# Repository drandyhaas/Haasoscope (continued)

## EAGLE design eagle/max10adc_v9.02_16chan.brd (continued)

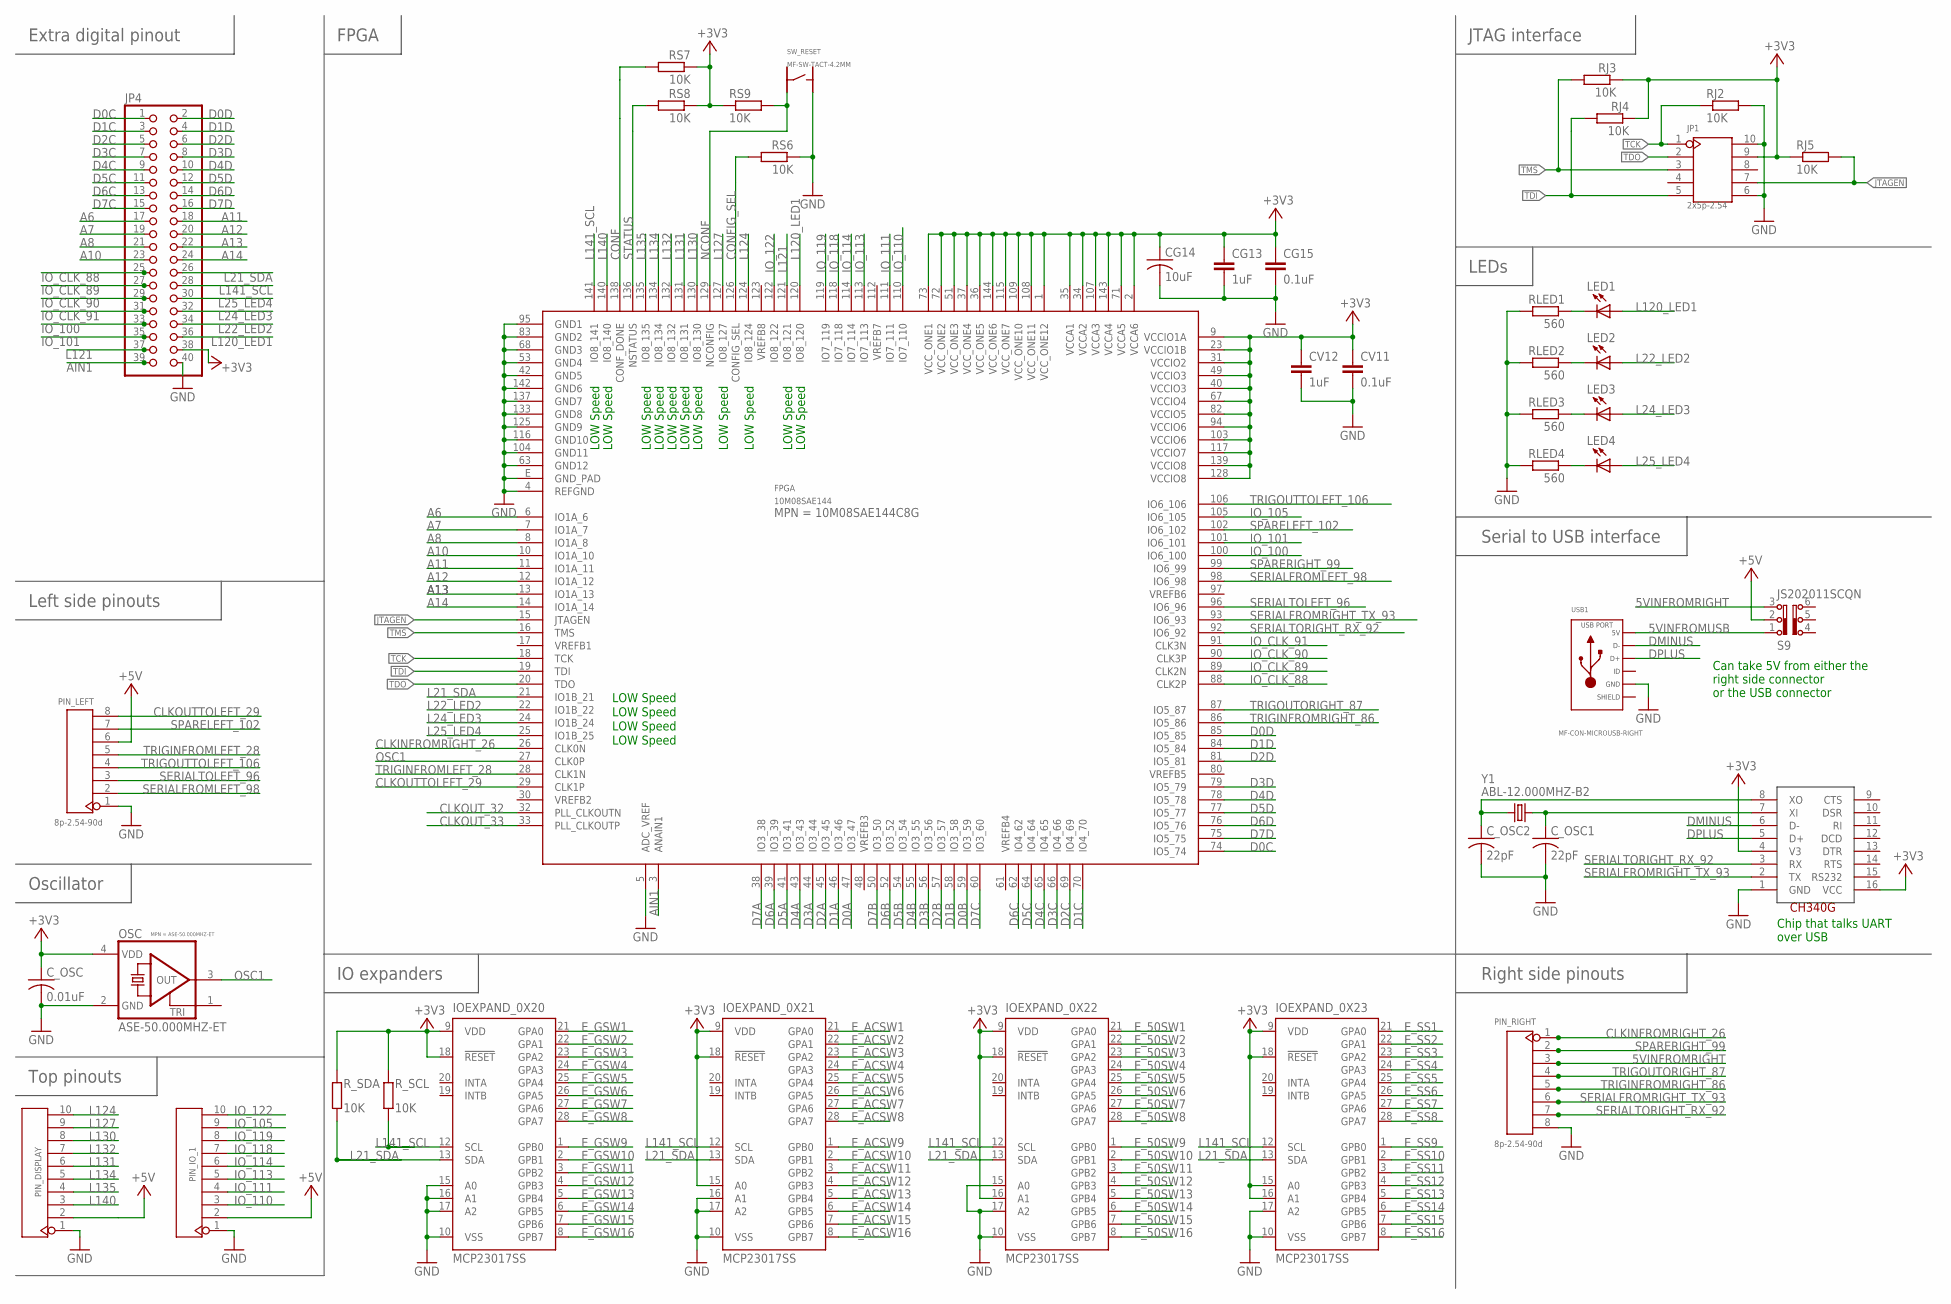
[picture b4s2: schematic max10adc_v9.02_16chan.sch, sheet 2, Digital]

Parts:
CG13: 1uF; C0805K; MPN MF-CAP-0805-1uF
CG14: 10uF; C1206; MPN MF-CAP-1206-10uF
CG15: 0.1uF; C0805K; MPN MF-CAP-0805-0.1uF
CV11: 0.1uF; C0805K; MPN MF-CAP-0805-0.1uF
CV12: 1uF; C0805K; MPN MF-CAP-0805-1uF
C_OSC: 0.01uF; C0603
C_OSC1, C_OSC2: 22pF; C0603
FPGA: 10M08SAE144; EQFP144; MPN 10M08SAE144C8G
IOEXPAND_0X20, IOEXPAND_0X21, IOEXPAND_0X22, IOEXPAND_0X23: MCP23017SS; SSOP28
JP1: 2x5p-2.54; H2X5-2.54
JP4: PINHD-2X20/90; 2X20/90
LED1, LED2, LED3, LED4: MF-LED-0805-RED; SML0805; MPN MF-LED-0805-RED
OSC: ASE-50.000MHZ-ET; ASE; MPN ASE-50.000MHZ-ET
PIN_DISPLAY: YELLOW-10P-2.54; H10-2.54
PIN_IO_1: YELLOW-10P-2.54; H10-2.54
PIN_LEFT: 8p-2.54-90d; H8-2.54-90D-MALE
PIN_RIGHT: 8p-2.54-90d; H8-2.54-90D-FEMALE
RJ2, RJ3, RJ4, RJ5: 10K; R0805; MPN MF-RES-0805-10K
RLED1, RLED2, RLED3, RLED4: 560; R0805; MPN MF-RES-0805-560
RS6, RS7, RS8, RS9: 10K; R0805; MPN MF-RES-0805-10K
R_SCL: 10K; R0805; MPN MF-RES-0805-10K
R_SDA: 10K; R0805; MPN MF-RES-0805-10K
S9: JS202011SCQN
SW_RESET: MF-SW-TACT-4.2MM; TACT4.2MM
U340G: CH340G; SOIC16
USB1: MF-CON-MICROUSB-RIGHT; 10118193-0001LF
Y1: ABL-12.000MHZ-B2; HC49US

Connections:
5VINFROMRIGHT: PIN_RIGHT.3, S9.3
5VINFROMUSB: S9.1, USB1.1 (5V)
+3V3: CG13.1, CG14.1, CG15.1, CV11.1, CV12.1, C_OSC.1, FPGA.1 (VCC_ONE12), FPGA.2 (VCCA6), FPGA.9 (VCCIO1A), FPGA.23 (VCCIO1B), FPGA.31 (VCCIO2), FPGA.34 (VCCA2), FPGA.35 (VCCA1), FPGA.36 (VCC_ONE5), FPGA.37 (VCC_ONE4), FPGA.40 (VCCIO3), FPGA.49 (VCCIO3), FPGA.51 (VCC_ONE3), FPGA.67 (VCCIO4), FPGA.71 (VCCA5), FPGA.72 (VCC_ONE2), FPGA.73 (VCC_ONE1), FPGA.82 (VCCIO5), FPGA.94 (VCCIO6), FPGA.103 (VCCIO6), FPGA.107 (VCCA3), FPGA.108 (VCC_ONE11), FPGA.109 (VCC_ONE10), FPGA.115 (VCC_ONE7), FPGA.117 (VCCIO7), FPGA.128 (VCCIO8), FPGA.139 (VCCIO8), FPGA.143 (VCCA4), FPGA.144 (VCC_ONE6), IOEXPAND_0X20.9 (VDD), IOEXPAND_0X20.18 (!RESET), IOEXPAND_0X21.9 (VDD), IOEXPAND_0X21.15 (A0), IOEXPAND_0X21.18 (!RESET), IOEXPAND_0X22.9 (VDD), IOEXPAND_0X22.16 (A1), IOEXPAND_0X22.18 (!RESET), IOEXPAND_0X23.9 (VDD), IOEXPAND_0X23.15 (A0), IOEXPAND_0X23.16 (A1), IOEXPAND_0X23.18 (!RESET), JP1.9, JP4.38, OSC.4 (VDD), RJ3.1, RJ4.1, RJ5.1, RS7.1, RS8.1, RS9.1, R_SCL.2, R_SDA.2, U340G.4 (V3), U340G.16 (VCC); also elsewhere on the board
+5V: PIN_DISPLAY.2, PIN_IO_1.2, PIN_LEFT.6, S9.2; also elsewhere on the board
A6: FPGA.6 (IO1A_6), JP4.17
A7: FPGA.7 (IO1A_7), JP4.19
A8: FPGA.8 (IO1A_8), JP4.21
A10: FPGA.10 (IO1A_10), JP4.23
A11: FPGA.11 (IO1A_11), JP4.18
A12: FPGA.12 (IO1A_12), JP4.20
A13: FPGA.13 (IO1A_13), JP4.22
A14: FPGA.14 (IO1A_14), JP4.24
AIN1: FPGA.3 (ANAIN1), JP4.39; also elsewhere on the board
CLKINFROMRIGHT_26: FPGA.26 (CLK0N), PIN_RIGHT.1
CLKOUTTOLEFT_29: FPGA.29 (CLK1P), PIN_LEFT.8
CLKOUT_32: FPGA.32 (PLL_CLKOUTN); also elsewhere on the board
CLKOUT_33: FPGA.33 (PLL_CLKOUTP); also elsewhere on the board
CONF: FPGA.138 (CONF_DONE), RS7.2
CONFIG_SEL: FPGA.126 (CONFIG_SEL), RS6.2
D0A: FPGA.47 (IO3_47); also elsewhere on the board
D0B: FPGA.59 (IO3_59); also elsewhere on the board
D0C: FPGA.74 (IO5_74), JP4.1
D0D: FPGA.85 (IO5_85), JP4.2
D1A: FPGA.46 (IO3_46); also elsewhere on the board
D1B: FPGA.58 (IO3_58); also elsewhere on the board
D1C: FPGA.70 (IO4_70), JP4.3
D1D: FPGA.84 (IO5_84), JP4.4
D2A: FPGA.45 (IO3_45); also elsewhere on the board
D2B: FPGA.57 (IO3_57); also elsewhere on the board
D2C: FPGA.69 (IO4_69), JP4.5
D2D: FPGA.81 (IO5_81), JP4.6
D3A: FPGA.44 (IO3_44); also elsewhere on the board
D3B: FPGA.56 (IO3_56); also elsewhere on the board
D3C: FPGA.66 (IO4_66), JP4.7
D3D: FPGA.79 (IO5_79), JP4.8
D4A: FPGA.43 (IO3_43); also elsewhere on the board
D4B: FPGA.55 (IO3_55); also elsewhere on the board
D4C: FPGA.65 (IO4_65), JP4.9
D4D: FPGA.78 (IO5_78), JP4.10
D5A: FPGA.41 (IO3_41); also elsewhere on the board
D5B: FPGA.54 (IO3_54); also elsewhere on the board
D5C: FPGA.64 (IO4_64), JP4.11
D5D: FPGA.77 (IO5_77), JP4.12
D6A: FPGA.39 (IO3_39); also elsewhere on the board
D6B: FPGA.52 (IO3_52); also elsewhere on the board
D6C: FPGA.62 (IO4_62), JP4.13
D6D: FPGA.76 (IO5_76), JP4.14
D7A: FPGA.38 (IO3_38); also elsewhere on the board
D7B: FPGA.50 (IO3_50); also elsewhere on the board
D7C: FPGA.60 (IO3_60), JP4.15
D7D: FPGA.75 (IO5_75), JP4.16
DMINUS: U340G.6 (D-), USB1.2 (D-)
DPLUS: U340G.5 (D+), USB1.3 (D+)
E_50SW1: IOEXPAND_0X22.21 (GPA0); also elsewhere on the board
E_50SW2: IOEXPAND_0X22.22 (GPA1); also elsewhere on the board
E_50SW3: IOEXPAND_0X22.23 (GPA2); also elsewhere on the board
E_50SW4: IOEXPAND_0X22.24 (GPA3); also elsewhere on the board
E_50SW5: IOEXPAND_0X22.25 (GPA4); also elsewhere on the board
E_50SW6: IOEXPAND_0X22.26 (GPA5); also elsewhere on the board
E_50SW7: IOEXPAND_0X22.27 (GPA6); also elsewhere on the board
E_50SW8: IOEXPAND_0X22.28 (GPA7); also elsewhere on the board
E_50SW9: IOEXPAND_0X22.1 (GPB0); also elsewhere on the board
E_50SW10: IOEXPAND_0X22.2 (GPB1); also elsewhere on the board
E_50SW11: IOEXPAND_0X22.3 (GPB2); also elsewhere on the board
E_50SW12: IOEXPAND_0X22.4 (GPB3); also elsewhere on the board
E_50SW13: IOEXPAND_0X22.5 (GPB4); also elsewhere on the board
E_50SW14: IOEXPAND_0X22.6 (GPB5); also elsewhere on the board
E_50SW15: IOEXPAND_0X22.7 (GPB6); also elsewhere on the board
E_50SW16: IOEXPAND_0X22.8 (GPB7); also elsewhere on the board
E_ACSW1: IOEXPAND_0X21.21 (GPA0); also elsewhere on the board
E_ACSW2: IOEXPAND_0X21.22 (GPA1); also elsewhere on the board
E_ACSW3: IOEXPAND_0X21.23 (GPA2); also elsewhere on the board
E_ACSW4: IOEXPAND_0X21.24 (GPA3); also elsewhere on the board
E_ACSW5: IOEXPAND_0X21.25 (GPA4); also elsewhere on the board
E_ACSW6: IOEXPAND_0X21.26 (GPA5); also elsewhere on the board
E_ACSW7: IOEXPAND_0X21.27 (GPA6); also elsewhere on the board
E_ACSW8: IOEXPAND_0X21.28 (GPA7); also elsewhere on the board
E_ACSW9: IOEXPAND_0X21.1 (GPB0); also elsewhere on the board
E_ACSW10: IOEXPAND_0X21.2 (GPB1); also elsewhere on the board
E_ACSW11: IOEXPAND_0X21.3 (GPB2); also elsewhere on the board
E_ACSW12: IOEXPAND_0X21.4 (GPB3); also elsewhere on the board
E_ACSW13: IOEXPAND_0X21.5 (GPB4); also elsewhere on the board
E_ACSW14: IOEXPAND_0X21.6 (GPB5); also elsewhere on the board
E_ACSW15: IOEXPAND_0X21.7 (GPB6); also elsewhere on the board
E_ACSW16: IOEXPAND_0X21.8 (GPB7); also elsewhere on the board
E_GSW1: IOEXPAND_0X20.21 (GPA0); also elsewhere on the board
E_GSW2: IOEXPAND_0X20.22 (GPA1); also elsewhere on the board
E_GSW3: IOEXPAND_0X20.23 (GPA2); also elsewhere on the board
E_GSW4: IOEXPAND_0X20.24 (GPA3); also elsewhere on the board
E_GSW5: IOEXPAND_0X20.25 (GPA4); also elsewhere on the board
E_GSW6: IOEXPAND_0X20.26 (GPA5); also elsewhere on the board
E_GSW7: IOEXPAND_0X20.27 (GPA6); also elsewhere on the board
E_GSW8: IOEXPAND_0X20.28 (GPA7); also elsewhere on the board
E_GSW9: IOEXPAND_0X20.1 (GPB0); also elsewhere on the board
E_GSW10: IOEXPAND_0X20.2 (GPB1); also elsewhere on the board
E_GSW11: IOEXPAND_0X20.3 (GPB2); also elsewhere on the board
E_GSW12: IOEXPAND_0X20.4 (GPB3); also elsewhere on the board
E_GSW13: IOEXPAND_0X20.5 (GPB4); also elsewhere on the board
E_GSW14: IOEXPAND_0X20.6 (GPB5); also elsewhere on the board
E_GSW15: IOEXPAND_0X20.7 (GPB6); also elsewhere on the board
E_GSW16: IOEXPAND_0X20.8 (GPB7); also elsewhere on the board
E_SS1: IOEXPAND_0X23.21 (GPA0); also elsewhere on the board
E_SS2: IOEXPAND_0X23.22 (GPA1); also elsewhere on the board
E_SS3: IOEXPAND_0X23.23 (GPA2); also elsewhere on the board
E_SS4: IOEXPAND_0X23.24 (GPA3); also elsewhere on the board
E_SS5: IOEXPAND_0X23.25 (GPA4); also elsewhere on the board
E_SS6: IOEXPAND_0X23.26 (GPA5); also elsewhere on the board
E_SS7: IOEXPAND_0X23.27 (GPA6); also elsewhere on the board
E_SS8: IOEXPAND_0X23.28 (GPA7); also elsewhere on the board
E_SS9: IOEXPAND_0X23.1 (GPB0); also elsewhere on the board
E_SS10: IOEXPAND_0X23.2 (GPB1); also elsewhere on the board
E_SS11: IOEXPAND_0X23.3 (GPB2); also elsewhere on the board
E_SS12: IOEXPAND_0X23.4 (GPB3); also elsewhere on the board
E_SS13: IOEXPAND_0X23.5 (GPB4); also elsewhere on the board
E_SS14: IOEXPAND_0X23.6 (GPB5); also elsewhere on the board
E_SS15: IOEXPAND_0X23.7 (GPB6); also elsewhere on the board
E_SS16: IOEXPAND_0X23.8 (GPB7); also elsewhere on the board
GND: CG13.2, CG14.2, CG15.2, CV11.2, CV12.2, C_OSC.2, C_OSC1.2, C_OSC2.2, FPGA.4 (REFGND), FPGA.5 (ADC_VREF), FPGA.42 (GND5), FPGA.53 (GND4), FPGA.63 (GND12), FPGA.68 (GND3), FPGA.83 (GND2), FPGA.95 (GND1), FPGA.104 (GND11), FPGA.116 (GND10), FPGA.125 (GND9), FPGA.133 (GND8), FPGA.137 (GND7), FPGA.142 (GND6), FPGA.E (GND_PAD), IOEXPAND_0X20.10 (VSS), IOEXPAND_0X20.15 (A0), IOEXPAND_0X20.16 (A1), IOEXPAND_0X20.17 (A2), IOEXPAND_0X21.10 (VSS), IOEXPAND_0X21.16 (A1), IOEXPAND_0X21.17 (A2), IOEXPAND_0X22.10 (VSS), IOEXPAND_0X22.15 (A0), IOEXPAND_0X22.17 (A2), IOEXPAND_0X23.10 (VSS), IOEXPAND_0X23.17 (A2), JP1.6, JP1.10, JP4.40, OSC.2 (GND), PIN_DISPLAY.1, PIN_IO_1.1, PIN_LEFT.1, PIN_RIGHT.8, RJ2.2, RLED1.2, RLED2.2, RLED3.2, RLED4.2, RS6.1, SW_RESET.P$2, U340G.1 (GND), USB1.5 (GND); also elsewhere on the board
IO_100: FPGA.100 (IO6_100), JP4.33; also elsewhere on the board
IO_101: FPGA.101 (IO6_101), JP4.35; also elsewhere on the board
IO_105: FPGA.105 (IO6_105), PIN_IO_1.9
IO_110: FPGA.110 (IO7_110), PIN_IO_1.3
IO_111: FPGA.111 (IO7_111), PIN_IO_1.4
IO_113: FPGA.113 (IO7_113), PIN_IO_1.5
IO_114: FPGA.114 (IO7_114), PIN_IO_1.6
IO_118: FPGA.118 (IO7_118), PIN_IO_1.7
IO_119: FPGA.119 (IO7_119), PIN_IO_1.8
IO_122: FPGA.122 (IO8_122), PIN_IO_1.10
IO_CLK_88: FPGA.88 (CLK2P), JP4.25
IO_CLK_89: FPGA.89 (CLK2N), JP4.27
IO_CLK_90: FPGA.90 (CLK3P), JP4.29
IO_CLK_91: FPGA.91 (CLK3N), JP4.31
JTAGEN: FPGA.15 (JTAGEN), JP1.7, RJ5.2
L21_SDA: FPGA.21 (IO1B_21), IOEXPAND_0X20.13 (SDA), IOEXPAND_0X21.13 (SDA), IOEXPAND_0X22.13 (SDA), IOEXPAND_0X23.13 (SDA), JP4.26, R_SDA.1; also elsewhere on the board
L22_LED2: FPGA.22 (IO1B_22), JP4.34, LED2.A
L24_LED3: FPGA.24 (IO1B_24), JP4.32, LED3.A
L25_LED4: FPGA.25 (IO1B_25), JP4.30, LED4.A
L120_LED1: FPGA.120 (IO8_120), JP4.36, LED1.A
L121: FPGA.121 (IO8_121), JP4.37; also elsewhere on the board
L124: FPGA.124 (IO8_124), PIN_DISPLAY.10
L127: FPGA.127 (IO8_127), PIN_DISPLAY.9
L130: FPGA.130 (IO8_130), PIN_DISPLAY.8
L131: FPGA.131 (IO8_131), PIN_DISPLAY.6
L132: FPGA.132 (IO8_132), PIN_DISPLAY.7
L134: FPGA.134 (IO8_134), PIN_DISPLAY.5
L135: FPGA.135 (IO8_135), PIN_DISPLAY.4
L140: FPGA.140 (IO8_140), PIN_DISPLAY.3
L141_SCL: FPGA.141 (IO8_141), IOEXPAND_0X20.12 (SCL), IOEXPAND_0X21.12 (SCL), IOEXPAND_0X22.12 (SCL), IOEXPAND_0X23.12 (SCL), JP4.28, R_SCL.1; also elsewhere on the board
unnamed: LED4.C, RLED4.1
unnamed: LED3.C, RLED3.1
unnamed: LED2.C, RLED2.1
unnamed: LED1.C, RLED1.1
unnamed: C_OSC1.1, U340G.7 (XI), Y1.1
unnamed: C_OSC2.1, U340G.8 (XO), Y1.2
NCONF: FPGA.129 (NCONFIG), RS9.2, SW_RESET.P$4
OSC1: FPGA.27 (CLK0P), OSC.3 (OUT)
SERIALFROMLEFT_98: FPGA.98 (IO6_98), PIN_LEFT.2
SERIALFROMRIGHT_TX_93: FPGA.93 (IO6_93), PIN_RIGHT.6, U340G.2 (TX)
SERIALTOLEFT_96: FPGA.96 (IO6_96), PIN_LEFT.3
SERIALTORIGHT_RX_92: FPGA.92 (IO6_92), PIN_RIGHT.7, U340G.3 (RX)
SLD: USB1.S1 (SLD), USB1.S2 (SLD), USB1.S3 (SLD), USB1.S4 (SLD)
SPARELEFT_102: FPGA.102 (IO6_102), PIN_LEFT.7
SPARERIGHT_99: FPGA.99 (IO6_99), PIN_RIGHT.2
STATUS: FPGA.136 (NSTATUS), RS8.2
TCK: FPGA.18 (TCK), JP1.1, RJ2.1
TDI: FPGA.19 (TDI), JP1.5, RJ4.2
TDO: FPGA.20 (TDO), JP1.2
TMS: FPGA.16 (TMS), JP1.3, RJ3.2
TRIGINFROMLEFT_28: FPGA.28 (CLK1N), PIN_LEFT.5
TRIGINFROMRIGHT_86: FPGA.86 (IO5_86), PIN_RIGHT.5
TRIGOUTORIGHT_87: FPGA.87 (IO5_87), PIN_RIGHT.4
TRIGOUTTOLEFT_106: FPGA.106 (IO6_106), PIN_LEFT.4

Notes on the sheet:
LOW Speed
FPGA
Right side pinouts
Left side pinouts
Oscillator
Top pinouts
IO expanders
Serial to USB interface
LEDs
JTAG interface
Can take 5V from either the right side connector or the USB connector
Chip that talks UART over USB
Extra digital pinout

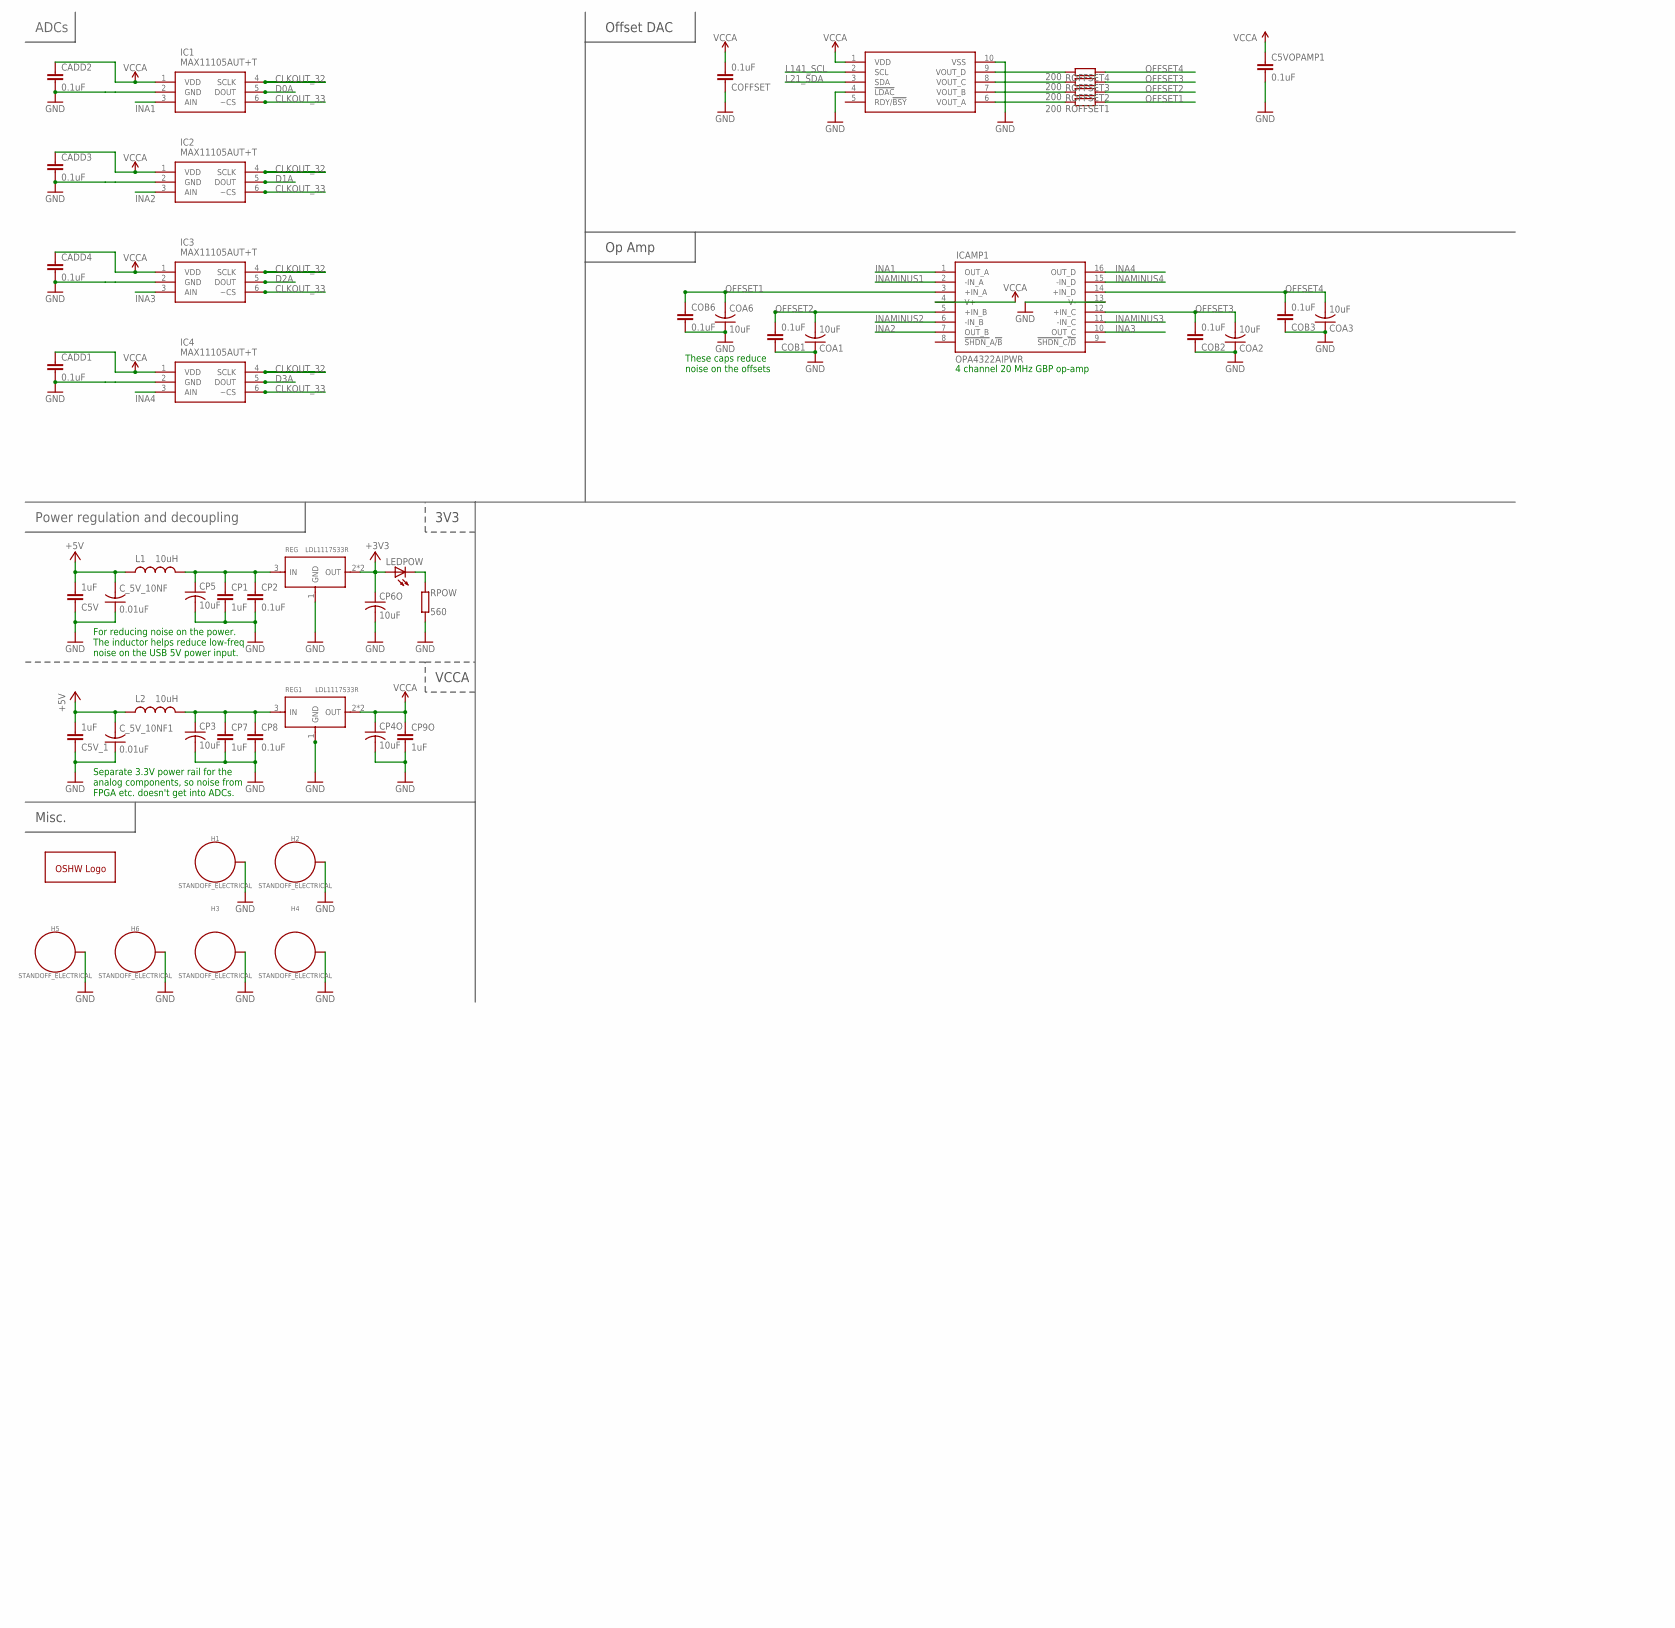
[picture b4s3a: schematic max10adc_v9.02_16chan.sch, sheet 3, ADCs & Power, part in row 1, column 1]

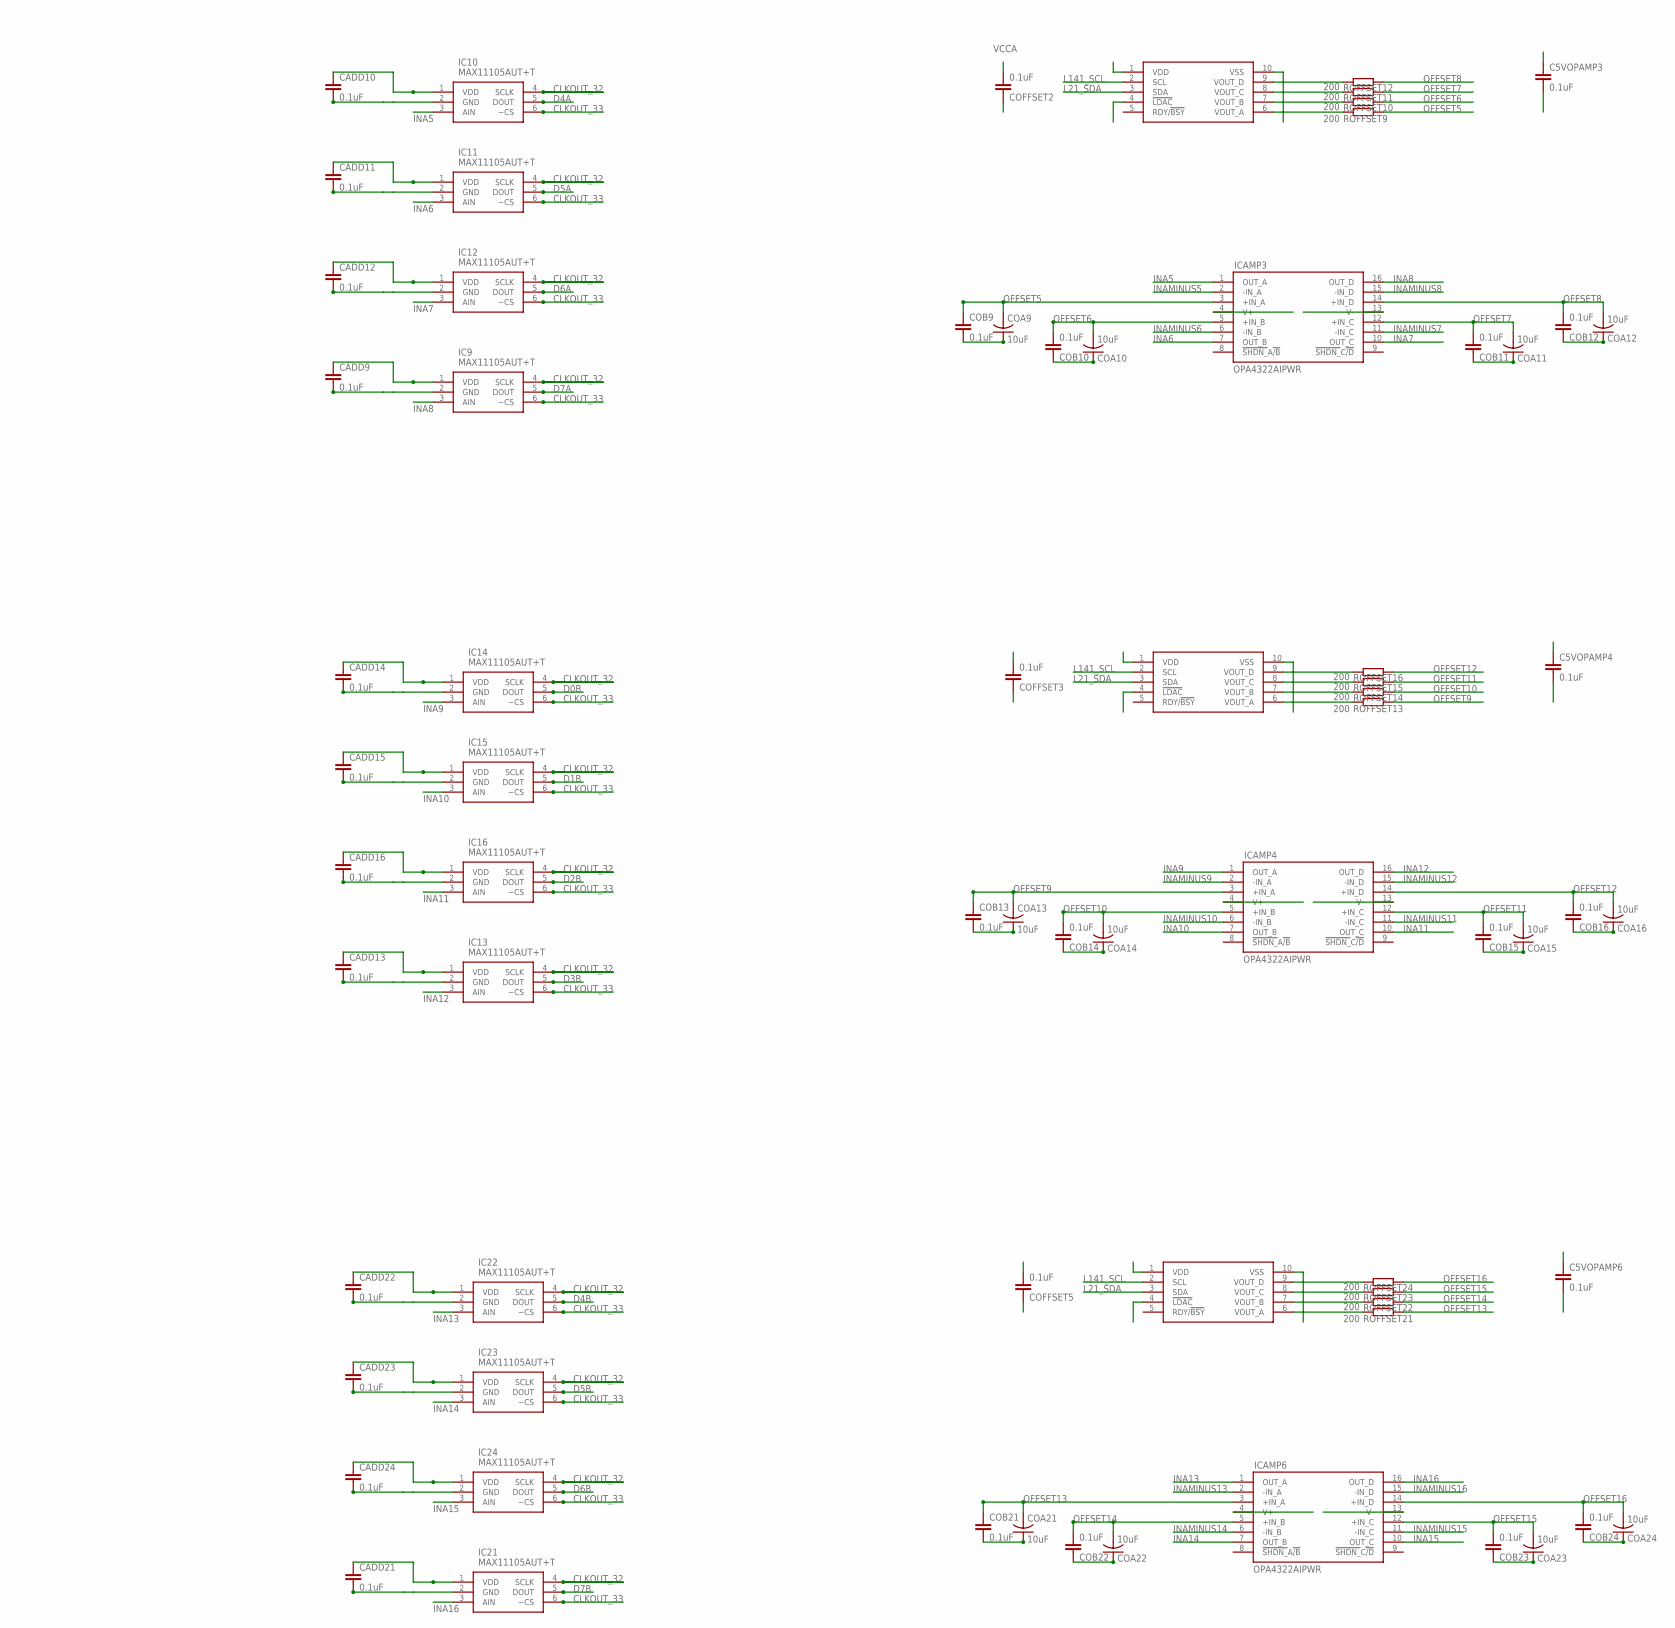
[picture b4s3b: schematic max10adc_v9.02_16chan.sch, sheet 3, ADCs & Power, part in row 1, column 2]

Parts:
C5V, C5V_1: 1uF; C0805K; MPN MF-CAP-0805-1uF
C5VOPAMP1, C5VOPAMP3, C5VOPAMP4, C5VOPAMP6: 0.1uF; C0805K; MPN MF-CAP-0805-0.1uF
CADD1, CADD2, CADD3, CADD4, CADD9, CADD10, CADD11, CADD12, CADD13, CADD14, CADD15, CADD16, CADD21, CADD22, CADD23, CADD24: 0.1uF; C0805K; MPN MF-CAP-0805-0.1uF
COA1, COA2, COA3, COA6, COA9, COA10, COA11, COA12, COA13, COA14, COA15, COA16, COA21, COA22, COA23, COA24: 10uF; C1206; MPN MF-CAP-1206-10uF
COB1, COB2, COB3, COB6, COB9, COB10, COB11, COB12, COB13, COB14, COB15, COB16, COB21, COB22, COB23, COB24: 0.1uF; C0805K; MPN MF-CAP-0805-0.1uF
COFFSET, COFFSET2, COFFSET3, COFFSET5: 0.1uF; C0805K; MPN MF-CAP-0805-0.1uF
CP1, CP7, CP9O: 1uF; C0805K; MPN MF-CAP-0805-1uF
CP2, CP8: 0.1uF; C0805K; MPN MF-CAP-0805-0.1uF
CP3, CP4O, CP5, CP6O: 10uF; C1206; MPN MF-CAP-1206-10uF
C_5V_10NF, C_5V_10NF1: 0.01uF; C0603
DAC1, DAC2, DAC3, DAC4: MCP4728; MSOP10
GOLD_ORB_SM1: OSHWLOGOLOGO8MM; OSHW_8MM
H1, H2, H3, H4, H5, H6: STANDOFF_ELECTRICAL; STANDOFF-ELECTRICAL
IC1, IC2, IC3, IC4, IC9, IC10, IC11, IC12, IC13, IC14, IC15, IC16, IC21, IC22, IC23, IC24: MAX11105AUT+T; SOT95P280X145-6N
ICAMP1, ICAMP3, ICAMP4, ICAMP6: OPA4322AIPWR; SOP65P640X120-16N
L1, L2: 10uH; 1210; MPN MF-IND-1210-10uH
LEDPOW: MF-LED-0805-RED; SML0805; MPN MF-LED-0805-RED
REG, REG1: LDL1117S33R; SOT-223; MPN LDL1117S33R
ROFFSET1, ROFFSET2, ROFFSET3, ROFFSET4, ROFFSET9, ROFFSET10, ROFFSET11, ROFFSET12, ROFFSET13, ROFFSET14, ROFFSET15, ROFFSET16, ROFFSET21, ROFFSET22, ROFFSET23, ROFFSET24: 200; R0805
RPOW: 560; R0805; MPN MF-RES-0805-560

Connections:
5VC3: CP3.1, CP7.1, CP8.1, L2.2, REG1.3 (IN)
5VC5: CP1.1, CP2.1, CP5.1, L1.2, REG.3 (IN)
+3V3: CP6O.1, LEDPOW.A, REG.2 (OUT), REG.TER (OUT); also elsewhere on the board
+5V: C5V.2, C5V_1.2, C_5V_10NF.2, C_5V_10NF1.2, L1.1, L2.1; also elsewhere on the board
CLKOUT_32: IC1.4 (SCLK), IC2.4 (SCLK), IC3.4 (SCLK), IC4.4 (SCLK), IC9.4 (SCLK), IC10.4 (SCLK), IC11.4 (SCLK), IC12.4 (SCLK), IC13.4 (SCLK), IC14.4 (SCLK), IC15.4 (SCLK), IC16.4 (SCLK), IC21.4 (SCLK), IC22.4 (SCLK), IC23.4 (SCLK), IC24.4 (SCLK); also elsewhere on the board
CLKOUT_33: IC1.6 (~CS), IC2.6 (~CS), IC3.6 (~CS), IC4.6 (~CS), IC9.6 (~CS), IC10.6 (~CS), IC11.6 (~CS), IC12.6 (~CS), IC13.6 (~CS), IC14.6 (~CS), IC15.6 (~CS), IC16.6 (~CS), IC21.6 (~CS), IC22.6 (~CS), IC23.6 (~CS), IC24.6 (~CS); also elsewhere on the board
D0A: IC1.5 (DOUT); also elsewhere on the board
D0B: IC14.5 (DOUT); also elsewhere on the board
D1A: IC2.5 (DOUT); also elsewhere on the board
D1B: IC15.5 (DOUT); also elsewhere on the board
D2A: IC3.5 (DOUT); also elsewhere on the board
D2B: IC16.5 (DOUT); also elsewhere on the board
D3A: IC4.5 (DOUT); also elsewhere on the board
D3B: IC13.5 (DOUT); also elsewhere on the board
D4A: IC10.5 (DOUT); also elsewhere on the board
D4B: IC22.5 (DOUT); also elsewhere on the board
D5A: IC11.5 (DOUT); also elsewhere on the board
D5B: IC23.5 (DOUT); also elsewhere on the board
D6A: IC12.5 (DOUT); also elsewhere on the board
D6B: IC24.5 (DOUT); also elsewhere on the board
D7A: IC9.5 (DOUT); also elsewhere on the board
D7B: IC21.5 (DOUT); also elsewhere on the board
GND: C5V.1, C5VOPAMP1.2, C5VOPAMP3.2, C5VOPAMP4.2, C5VOPAMP6.2, C5V_1.1, CADD1.2, CADD2.2, CADD3.2, CADD4.2, CADD9.2, CADD10.2, CADD11.2, CADD12.2, CADD13.2, CADD14.2, CADD15.2, CADD16.2, CADD21.2, CADD22.2, CADD23.2, CADD24.2, COA1.1, COA2.1, COA3.1, COA6.1, COA9.1, COA10.1, COA11.1, COA12.1, COA13.1, COA14.1, COA15.1, COA16.1, COA21.1, COA22.1, COA23.1, COA24.1, COB1.1, COB2.1, COB3.1, COB6.1, COB9.1, COB10.1, COB11.1, COB12.1, COB13.1, COB14.1, COB15.1, COB16.1, COB21.1, COB22.1, COB23.1, COB24.1, COFFSET.1, COFFSET2.1, COFFSET3.1, COFFSET5.1, CP1.2, CP2.2, CP3.2, CP4O.2, CP5.2, CP6O.2, CP7.2, CP8.2, CP9O.2, C_5V_10NF.1, C_5V_10NF1.1, DAC1.4 (!LDAC), DAC1.10 (VSS), DAC2.4 (!LDAC), DAC2.10 (VSS), DAC3.4 (!LDAC), DAC3.10 (VSS), DAC4.4 (!LDAC), DAC4.10 (VSS), H1.P1, H2.P1, H3.P1, H4.P1, H5.P1, H6.P1, IC1.2 (GND), IC2.2 (GND), IC3.2 (GND), IC4.2 (GND), IC9.2 (GND), IC10.2 (GND), IC11.2 (GND), IC12.2 (GND), IC13.2 (GND), IC14.2 (GND), IC15.2 (GND), IC16.2 (GND), IC21.2 (GND), IC22.2 (GND), IC23.2 (GND), IC24.2 (GND), ICAMP1.13 (V-), ICAMP3.13 (V-), ICAMP4.13 (V-), ICAMP6.13 (V-), REG.1 (GND), REG1.1 (GND), RPOW.2; also elsewhere on the board
INA1: IC1.3 (AIN), ICAMP1.1 (OUT_A); also elsewhere on the board
INA2: IC2.3 (AIN), ICAMP1.7 (OUT_B); also elsewhere on the board
INA3: IC3.3 (AIN), ICAMP1.10 (OUT_C); also elsewhere on the board
INA4: IC4.3 (AIN), ICAMP1.16 (OUT_D); also elsewhere on the board
INA5: IC10.3 (AIN), ICAMP3.1 (OUT_A); also elsewhere on the board
INA6: IC11.3 (AIN), ICAMP3.7 (OUT_B); also elsewhere on the board
INA7: IC12.3 (AIN), ICAMP3.10 (OUT_C); also elsewhere on the board
INA8: IC9.3 (AIN), ICAMP3.16 (OUT_D); also elsewhere on the board
INA9: IC14.3 (AIN), ICAMP4.1 (OUT_A); also elsewhere on the board
INA10: IC15.3 (AIN), ICAMP4.7 (OUT_B); also elsewhere on the board
INA11: IC16.3 (AIN), ICAMP4.10 (OUT_C); also elsewhere on the board
INA12: IC13.3 (AIN), ICAMP4.16 (OUT_D); also elsewhere on the board
INA13: IC22.3 (AIN), ICAMP6.1 (OUT_A); also elsewhere on the board
INA14: IC23.3 (AIN), ICAMP6.7 (OUT_B); also elsewhere on the board
INA15: IC24.3 (AIN), ICAMP6.10 (OUT_C); also elsewhere on the board
INA16: IC21.3 (AIN), ICAMP6.16 (OUT_D); also elsewhere on the board
INAMINUS1: ICAMP1.2 (-IN_A); also elsewhere on the board
INAMINUS2: ICAMP1.6 (-IN_B); also elsewhere on the board
INAMINUS3: ICAMP1.11 (-IN_C); also elsewhere on the board
INAMINUS4: ICAMP1.15 (-IN_D); also elsewhere on the board
INAMINUS5: ICAMP3.2 (-IN_A); also elsewhere on the board
INAMINUS6: ICAMP3.6 (-IN_B); also elsewhere on the board
INAMINUS7: ICAMP3.11 (-IN_C); also elsewhere on the board
INAMINUS8: ICAMP3.15 (-IN_D); also elsewhere on the board
INAMINUS9: ICAMP4.2 (-IN_A); also elsewhere on the board
INAMINUS10: ICAMP4.6 (-IN_B); also elsewhere on the board
INAMINUS11: ICAMP4.11 (-IN_C); also elsewhere on the board
INAMINUS12: ICAMP4.15 (-IN_D); also elsewhere on the board
INAMINUS13: ICAMP6.2 (-IN_A); also elsewhere on the board
INAMINUS14: ICAMP6.6 (-IN_B); also elsewhere on the board
INAMINUS15: ICAMP6.11 (-IN_C); also elsewhere on the board
INAMINUS16: ICAMP6.15 (-IN_D); also elsewhere on the board
L21_SDA: DAC1.3 (SDA), DAC2.3 (SDA), DAC3.3 (SDA), DAC4.3 (SDA); also elsewhere on the board
L141_SCL: DAC1.2 (SCL), DAC2.2 (SCL), DAC3.2 (SCL), DAC4.2 (SCL); also elsewhere on the board
unnamed: DAC2.6 (VOUT_A), ROFFSET9.2
unnamed: DAC2.7 (VOUT_B), ROFFSET10.2
unnamed: DAC2.8 (VOUT_C), ROFFSET11.2
unnamed: DAC2.9 (VOUT_D), ROFFSET12.2
unnamed: DAC3.6 (VOUT_A), ROFFSET13.2
unnamed: DAC3.7 (VOUT_B), ROFFSET14.2
unnamed: DAC3.8 (VOUT_C), ROFFSET15.2
unnamed: DAC3.9 (VOUT_D), ROFFSET16.2
unnamed: LEDPOW.C, RPOW.1
unnamed: DAC4.6 (VOUT_A), ROFFSET21.2
unnamed: DAC4.7 (VOUT_B), ROFFSET22.2
unnamed: DAC4.8 (VOUT_C), ROFFSET23.2
unnamed: DAC1.6 (VOUT_A), ROFFSET1.2
unnamed: DAC1.7 (VOUT_B), ROFFSET2.2
unnamed: DAC1.8 (VOUT_C), ROFFSET3.2
unnamed: DAC1.9 (VOUT_D), ROFFSET4.2
unnamed: DAC4.9 (VOUT_D), ROFFSET24.2
OFFSET1: COA6.2, COB6.2, ICAMP1.3 (+IN_A), ROFFSET1.1
OFFSET2: COA1.2, COB1.2, ICAMP1.5 (+IN_B), ROFFSET2.1
OFFSET3: COA2.2, COB2.2, ICAMP1.12 (+IN_C), ROFFSET3.1
OFFSET4: COA3.2, COB3.2, ICAMP1.14 (+IN_D), ROFFSET4.1
OFFSET5: COA9.2, COB9.2, ICAMP3.3 (+IN_A), ROFFSET9.1
OFFSET6: COA10.2, COB10.2, ICAMP3.5 (+IN_B), ROFFSET10.1
OFFSET7: COA11.2, COB11.2, ICAMP3.12 (+IN_C), ROFFSET11.1
OFFSET8: COA12.2, COB12.2, ICAMP3.14 (+IN_D), ROFFSET12.1
OFFSET9: COA13.2, COB13.2, ICAMP4.3 (+IN_A), ROFFSET13.1
OFFSET10: COA14.2, COB14.2, ICAMP4.5 (+IN_B), ROFFSET14.1
OFFSET11: COA15.2, COB15.2, ICAMP4.12 (+IN_C), ROFFSET15.1
OFFSET12: COA16.2, COB16.2, ICAMP4.14 (+IN_D), ROFFSET16.1
OFFSET13: COA21.2, COB21.2, ICAMP6.3 (+IN_A), ROFFSET21.1
OFFSET14: COA22.2, COB22.2, ICAMP6.5 (+IN_B), ROFFSET22.1
OFFSET15: COA23.2, COB23.2, ICAMP6.12 (+IN_C), ROFFSET23.1
OFFSET16: COA24.2, COB24.2, ICAMP6.14 (+IN_D), ROFFSET24.1
VCCA: C5VOPAMP1.1, C5VOPAMP3.1, C5VOPAMP4.1, C5VOPAMP6.1, CADD1.1, CADD2.1, CADD3.1, CADD4.1, CADD9.1, CADD10.1, CADD11.1, CADD12.1, CADD13.1, CADD14.1, CADD15.1, CADD16.1, CADD21.1, CADD22.1, CADD23.1, CADD24.1, COFFSET.2, COFFSET2.2, COFFSET3.2, COFFSET5.2, CP4O.1, CP9O.1, DAC1.1 (VDD), DAC2.1 (VDD), DAC3.1 (VDD), DAC4.1 (VDD), IC1.1 (VDD), IC2.1 (VDD), IC3.1 (VDD), IC4.1 (VDD), IC9.1 (VDD), IC10.1 (VDD), IC11.1 (VDD), IC12.1 (VDD), IC13.1 (VDD), IC14.1 (VDD), IC15.1 (VDD), IC16.1 (VDD), IC21.1 (VDD), IC22.1 (VDD), IC23.1 (VDD), IC24.1 (VDD), ICAMP1.4 (V+), ICAMP3.4 (V+), ICAMP4.4 (V+), ICAMP6.4 (V+), REG1.2 (OUT), REG1.TER (OUT); also elsewhere on the board

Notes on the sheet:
ADCs
Power regulation and decoupling
3V3
VCCA
Misc.
For reducing noise on the power. The inductor helps reduce low-freq noise on the USB 5V power input.
Separate 3.3V power rail for the analog components, so noise from FPGA etc. doesn't get into ADCs.
Offset DAC
4 channel 20 MHz GBP op-amp
These caps reduce noise on the offsets
Op Amp

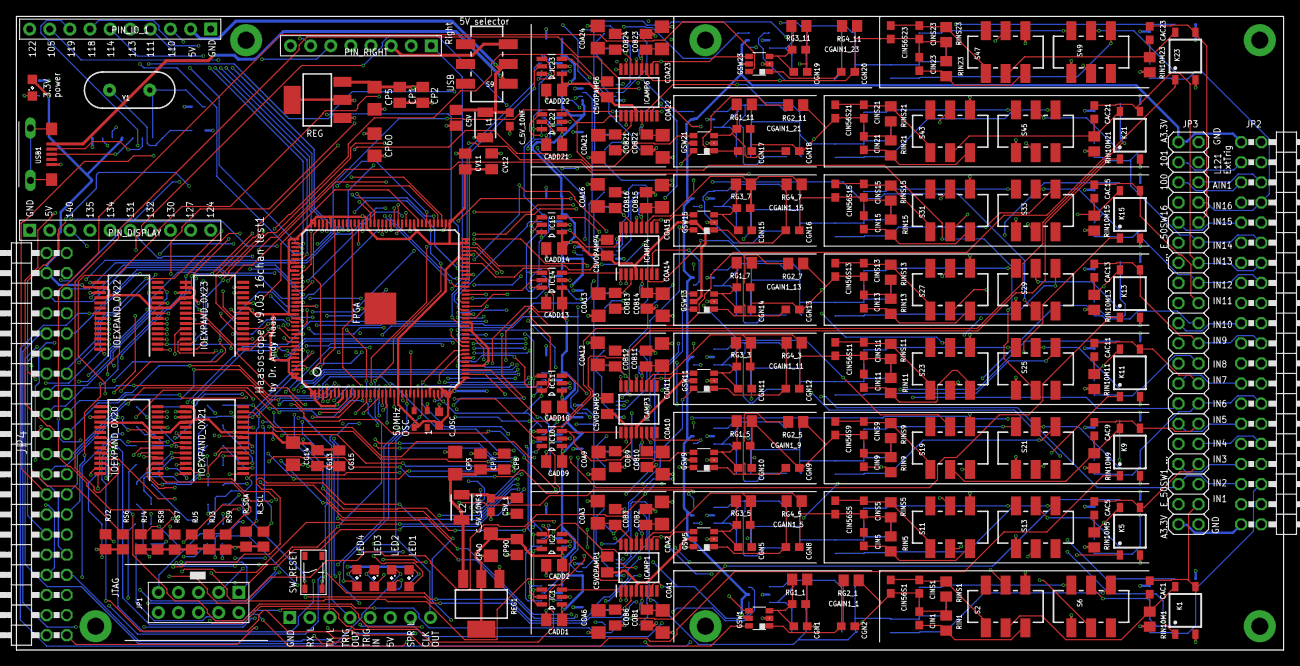
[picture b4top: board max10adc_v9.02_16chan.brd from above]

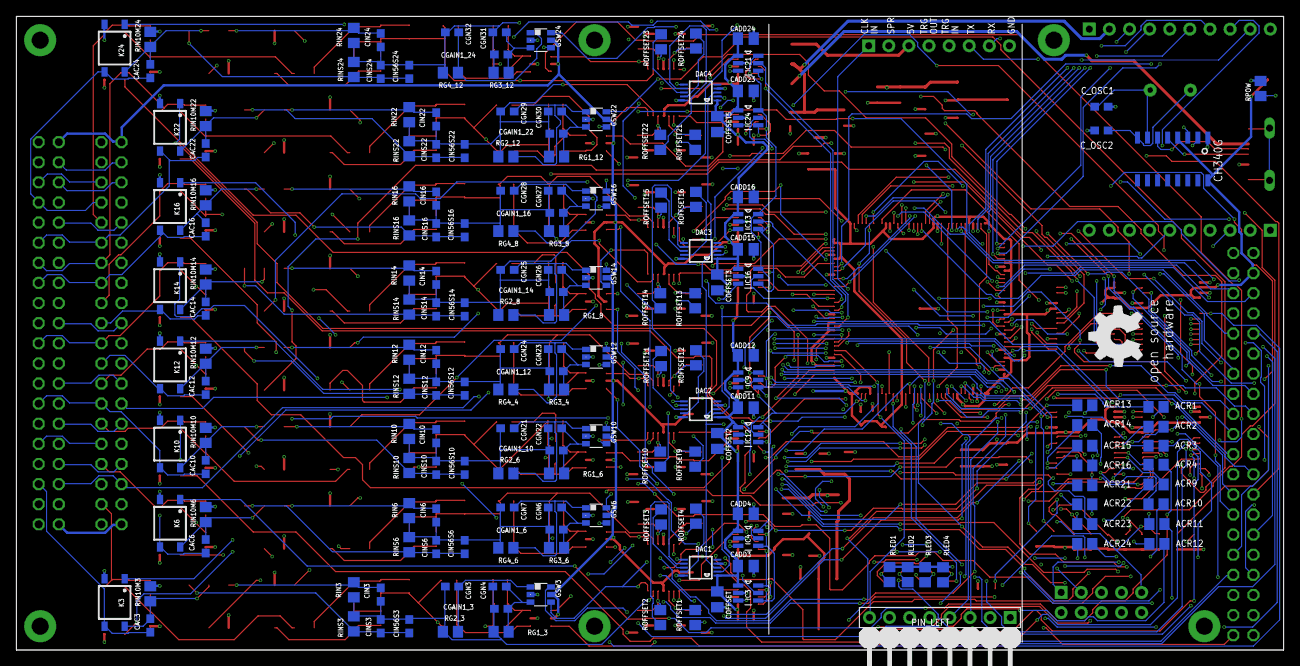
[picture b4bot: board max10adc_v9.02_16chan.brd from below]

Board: 4 copper layers, 160.0 x 80.0 mm, 423 parts (179 on the bottom side), 352 nets.
